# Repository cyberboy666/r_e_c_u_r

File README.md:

# r_e_c_u_r

 an open diy video sampler
 
 ![vectorfront][vectorfront]
 
__r_e_c_u_r__ is an embedded python/openframeworks application on _raspberry pi3_ that uses `input` from the _keypad_ to control  `video` while displaying a simple text ui on a _rpi lcd screen_ 

## in-depth video demo

[![video-walkthrough][video-thumbnail]](http://www.youtube.com/watch?v=FKKDr7pLpp0)

## features

- seamlessly loop video through rpi's HDMI or composite out
- intuitively _browse_ video files from external and internal disk and map them into __r_e_c_u_r__
- load and trigger video samples from numbered slots in the _sampler_ bank
- dynamically set and clear the start/end points of each sample as it plays
- control and sequence all inputs and more with midi-usb
- many sampler modes for varied playback including: repeat, one-shot, gated, random, fixed-length, random-start and more 
- exhaustive and extendable _settings_ menu  to suit your use

## extensions

as of _V2.0_ the __r_e_c_u_r__ platform has been extended in a number of directions to complement live performance and  _\_recur\__ , the original video playing engine:

- _\_captur\__ : input live video via CSI or USB , for live sampling and processing
- _\_conjur\__ : glsl shader engine, map and trigger shader files and control parameters in real time; generate video or process and mix existing sources
- _\_detour\__ : in-memory frame sampling (up to 500 frames), video scrubbing, playback speed and direction control, finger drumming
- toggling internal feedback + strobe effect 

_NOTE: most of the new V2.0 features are optimised for sd composite video output. Some of these extensions will work over HDMI but they are not fully supported - especially the live video input struggles_

### extension video walkthroughs

- [![conjur_walkthrough][conjur_thumbnail]](https://www.youtube.com/watch?v=ah2HY1fuv8w)
- [![captur_walkthrough][captur_thumbnail]](https://www.youtube.com/watch?v=e7m_YHEFahs)
- [![detour_walkthrough][detour_thumbnail]](https://www.youtube.com/watch?v=e9vrzn7c9R8)

## main objectives:

- *Affordable* : reducing the entry cost to performing with video
- *Extendable* : laying the foundations (of a user interface and code style) that can be easily iterated on by the community
- *Simple* : easy to operate (abstracted completely from ‘driving’ a raspi ) , easy to build (no technical computer install-y or circuit-y knowledge required to diy) , easy to develop (human readable code, inviting amateur/first time coders to contribute)

## documentation:

- [operating] - how to use r_e_c_u_r
- [building] - how to diy r_e_c_u_r
- [developing] - how to contribute to r_e_c_u_r

many other things documented on the [wiki]

## status

The nature of this project is to be open-ended and community driven. my r_e_c_u_r already solves the problems i initially built it for. what happens next depends on how it is used and received by you. if you like the idea please let me know / get involved !

## contact, donation and thanks

langolierz@gmail.com

you can find me (and others) at https://scanlines.xyz , an online diy av community space. theres a r_e_c_u_r channel in the chatroom: https://chat.scanlines.xyz/channel/r_e_c_u_r
there is also a facebook user group : https://www.facebook.com/groups/114465402691215/

all feedback is appreciated. if you want to donate to this project you can do so with the above email via paypal : everything i receive will go into improving __r_e_c_u_r__. cheers to Leo Browning for the 3d modelling and vector art and to Ben Caldwell for heaps of help with the code!

[vectorfront]: ./enclosure/vectorfront_keys.png
[video-thumbnail]: https://github.com/langolierz/r_e_c_u_r/wiki/images/video-thumbnail.jpg
[conjur_thumbnail]: https://github.com/langolierz/r_e_c_u_r/wiki/images/conjur_video_thumbnail.jpg
[captur_thumbnail]: https://github.com/langolierz/r_e_c_u_r/wiki/images/captur_video_thumbnail.jpg
[detour_thumbnail]: https://github.com/langolierz/r_e_c_u_r/wiki/images/detour_video_thumbnail.jpg
[operating]: https://github.com/langolierz/r_e_c_u_r/wiki/operate_docs
[building]: https://github.com/langolierz/r_e_c_u_r/wiki/build_docs
[developing]: https://github.com/langolierz/r_e_c_u_r/wiki/develop_docs
[wiki]: https://github.com/langolierz/r_e_c_u_r/wiki

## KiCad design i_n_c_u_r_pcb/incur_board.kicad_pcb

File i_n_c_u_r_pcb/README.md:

# i_n_c_u_r extension files have moved

you can now find all info and source regarding the i_n_c_u_r circuit [here](https://github.com/cyberboy666/i_n_c_u_r)

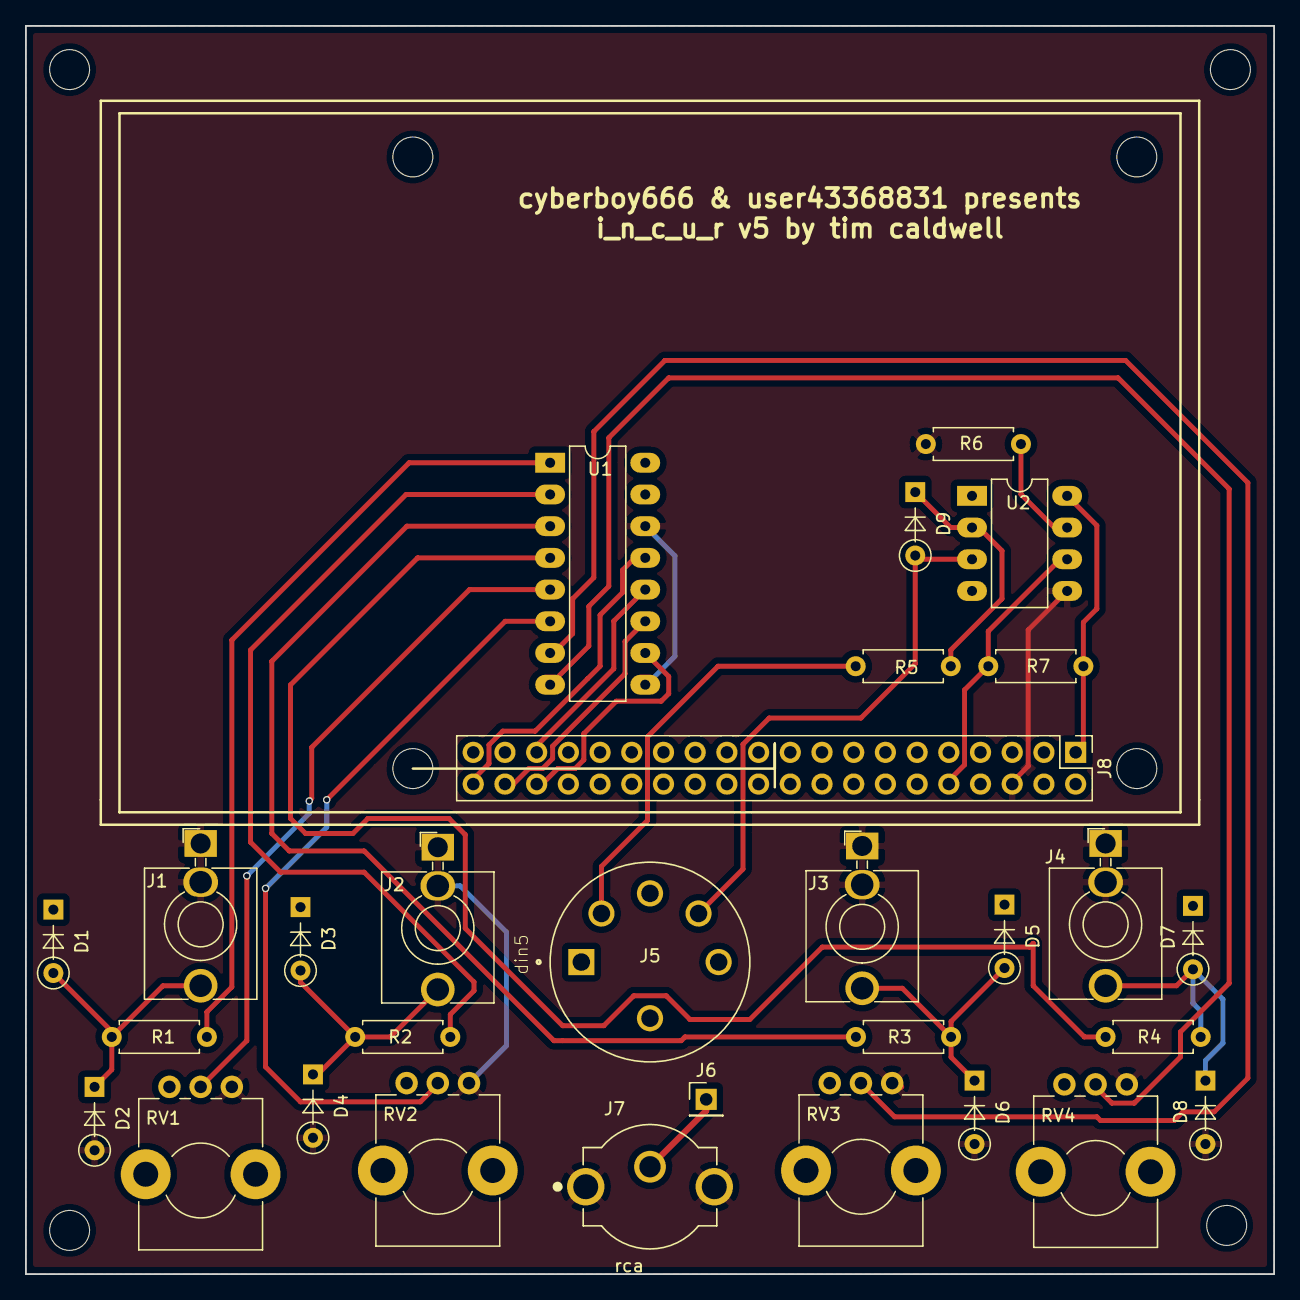
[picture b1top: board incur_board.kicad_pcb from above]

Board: 2 copper layers, 100.0 x 100.0 mm, 30 parts (0 on the bottom side), 25 nets.

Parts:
D1, D2, D3, D4, D5, D6, D7, D8: BAT46; D_DO-35_SOD27_P5.08mm_Vertical_KathodeUp
D9: 1N4148; D_DO-35_SOD27_P5.08mm_Vertical_KathodeUp
J1, J2, J3, J4: mono_jack_3.5mm; Jack_3.5mm_QingPu_WQP-PJ398SM_Vertical_CircularHoles
J5: din5; tht_vertical_din5
J6: Conn_01x01; Pin_Header_Straight_1x01_Pitch2.54mm
J7: rca; tht_rca_vertical
J8: 2x20_Extra_Tall_Header; PinHeader_2x20_P2.54mm_Vertical
R1, R2, R3, R4: 1K; R_Axial_DIN0207_L6.3mm_D2.5mm_P7.62mm_Horizontal
R5: 220; R_Axial_DIN0207_L6.3mm_D2.5mm_P7.62mm_Horizontal
R6: 100K; R_Axial_DIN0207_L6.3mm_D2.5mm_P7.62mm_Horizontal
R7: 470; R_Axial_DIN0207_L6.3mm_D2.5mm_P7.62mm_Horizontal
RV1, RV2, RV3, RV4: 10k_pot; tht_vertical_potentiometer
U1: MCP3008; DIP-16_W7.62mm_LongPads
U2: 6N138; DIP-8_W7.62mm_LongPads

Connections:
+3V3: J8.1, R7.2, U2.8
+5V: D1.1, D3.1, D5.1, D7.1, J8.2, RV1.1, RV2.1, RV3.1, RV4.1, U1.15, U1.16
A_IN_0: R1.1, U1.1
A_IN_1: R2.1, U1.2
A_IN_2: R3.1, U1.3
A_IN_3: R4.1, U1.4
A_IN_4: RV1.2, U1.5
A_IN_5: RV2.2, U1.6
A_IN_6: RV3.2, U1.7
A_IN_7: RV4.2, U1.8
CLK: J8.40, U1.13
CS: J8.36, U1.10
D_IN: J8.38, U1.11
D_OUT: J8.35, U1.12
GND: D2.2, D4.2, D6.2, D8.2, J1.2, J1.3, J2.2, J2.3, J3.2, J3.3, J4.2, J4.3, J7.2, J8.6, R6.1, RV1.3, RV2.3, RV3.3, RV4.3, U1.9, U1.14, U2.5
unnamed: D1.2, D2.1, J1.1, R1.2
unnamed: D3.2, D4.1, J2.1, R2.2
unnamed: D5.2, D6.1, J3.1, R3.2
unnamed: D7.2, D8.1, J4.1, R4.2
unnamed: D9.1, R5.1, U2.2
unnamed: D9.2, J5.5, U2.3
unnamed: J5.4, R5.2
unnamed: J6.1, J7.1
unnamed: R6.2, U2.7
RX: J8.10, R7.1, U2.6

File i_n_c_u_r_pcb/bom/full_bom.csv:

sku,qty,ref,val
A-1095,8,D1 D2 D3 D4 D5 D6 D7 D8 ,BAT46
A-157,1,D9 ,1N4148
A-2563,4,J1 J2 J3 J4 ,mono_jack_3.5mm
490-SD-50BV,1,J5 ,din5
-,1,J6 ,Conn_01x01
490-RCJ-024,1,J7 ,rca
485-1979,1,J8 ,2x20_Extra_Tall_Header
A-2200,4,R1 R2 R3 R4 ,1K
A-2246,1,R5 ,220
A-2248,1,R6 ,100K
A-2247,1,R7 ,470
652-PTV09A-4025FB103,4,RV1 RV2 RV3 RV4 ,10k_pot
A-2470,1,U1 ,MCP3008
859-6N138,1,U2 ,6N138

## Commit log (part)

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2019-09-08 Create notes_on_demo_video
2019-09-08 Rename notes_on_demo_video to notes_on_demo_video.md
2019-11-29 wip new shader banks feature
2019-12-03 adding strobe feature
2019-12-06 fixing update code
2019-12-07 map generic bank/slot midi command eg 'play_shader_0_0' to method
2019-12-08 v minor update
2019-12-09 experimental branch for implementing "akai apc key 25" visual feedback by lighting the led buttons to indicate shaders playing (early test)
2019-12-09 update svgs
2019-12-10 fix shader layer offset problem
2019-12-11 fix update code
2019-12-12 still untested, but think this should turn off all LEDs corresponding to unselected slots, while turning on the LEDs for selected slots
2019-12-13 its rough, but it works to indicate the currently playing shader on each layer!
2019-12-13 indicate which shader layer is selected by flashing the 'send' button. you can move up/down layers using 'send'/'device' respectively.
2019-12-14 merged and sorts shaders now too
2019-12-14 added toggle_x3_as_speed as a command available to midi map, and added a script to generate a helpful list of available actions
2019-12-14 Adds ability to have alternative MIDI mappings trigger when FN is held down. Use eg FN_DEFAULT to specify
2019-12-14 Feedback when camera preview is on
2019-12-15 fix boot bug
2019-12-15 Rough 'plugin' architecture, only supporting MIDI feedback right now
2019-12-15 Fix wrong indicator of 'preview' mode
2019-12-15 example of a macro running in a midi actions plugin
2019-12-15 'run_automation' example that triggers parameter changes
2019-12-15 MidiActionsPlugin -> ActionsPlugin, SequencePlugin has toggle functions (pause doesn't quite work right so need to come back and fix this)
2019-12-16 slight tidy and add pause_automation command separate from toggle_pause_automation (which still doesnt work like intended)
2019-12-17 Added base methods for plugin types that throw NotImplementedError if not overridden
2019-12-18 halfway to having working 'shader preset' banks
2019-12-19 fix argument order in plugins too
2019-12-19 ahhh fixed the bug!!! midi-mapped presets basically work now!
2019-12-19 Presets are now persisted between boots! With save/load json folder for plugins. Also fixed shader feedback state not updatingx
2019-12-19 SequencePlugin loops now
2019-12-19 move the routes back because they dont work, friendlier error message when no method found to handle route
2019-12-20 whew! record and playback shader automation parameters and persist to disk
2019-12-20 dont switch shaders if already selected
2019-12-21 stage 1 refactor shader param frame handling
2019-12-21 next stage refactor
2019-12-22 fix last (ha!) bug with recording loop automation, tidy up debug output
2019-12-22 wip osc and node server
2019-12-22 basic apc feedback for automation clips
2019-12-22 refactor some things
2019-12-22 fix range of param routes, add better debugging if no action found
2019-12-23 none-working
2019-12-23 osc responds to values 0-1 now
2019-12-23 tidy up
2019-12-23 renamed
2019-12-23 remove some crap from sight
2019-12-23 better control & feedback for shader quick presets (clear_current_frame and feedback indicates empty/selected slots)
2019-12-23 improve feedback
2019-12-24 improved generate-list-actions output
2019-12-24 improved generate-list-actions and added pregenerated documentation
2019-12-24 Improved auto-generated actions
2019-12-24 strip out some less-useful actions
2019-12-24 remove try_remove_file
2019-12-24 store/recall x3_as_speed setting in macros/automation
2019-12-24 fix some bugs that had crept in during refactoring
2019-12-24 presets/automation stores strobe amount too now
2019-12-25 ffix action names, tidy up a little, added midi mappings for modulation to shift+knob4-7, untested
2019-12-27 updated ACTIONS.md
2019-12-27 backported enable_feedback and disable_feedback commands
2019-12-27 fix modulation
2019-12-27 mappings for external osc sound reactivity
2019-12-27 tidy up some debug output, do quick checks first in get_ignored
2019-12-27 4 modulation inputs, effect levels assignable per-slot-per-layer, averages together modulation values from multiple sources
2019-12-27 remove debug output
2019-12-28 update docs to reflect new modulation changes
2019-12-28 quick little python script to read from microphone/line in and output OSC volume
2019-12-28 reset_modulation and reset_selected_modulation methods to help stay sane
2019-12-30 working proof of concept sending commands to an Arduino via serial (for use with https://github.com/doctea/veboard)
2020-01-01 send random commands to the serial device
2020-01-03 can send strings directly from midi mappings etc as routes accept strings now
2020-01-03 run soundreact along with recur
2020-01-05 adding to osc support
2020-01-05 remove FN_DEFAULT functionality since it is redundant, fixed config file
2020-01-05 more removal of redundant 'FN_DEFAULT' functionality
2020-01-05 re-add generic osc route
2020-01-10 log conjur output to a separate file
2020-01-10 Backported basic code for MIDI controller autodetection (custom config file per controller), plugins with example plugin, and Akai APC Key 25 feedback plugin
2020-01-10 enable the example test plugin
2020-01-10 tidied up a little
2020-01-10 fs tables
2020-01-14 can adjust speed of sequences by binding set_automation_speed, range is -2.0x to +2.0x
2020-01-14 update actions doc
2020-01-14 missed necessary file for midi input detection! also fix midi feedback not working if the shader plugins are not installed
2020-01-19 fix to prevent crash when non-APC Key was connected! silly typo
2020-01-19 Rough Launchpad custom controls with feedback
2020-01-31 rename MidiActionsTestPlugin to generic TestPlugin, remove mention of it in feedback plugin
2020-01-31 MultiActionsPlugin to allow mapping multiple actions to one binding using && to separate actions, eg action_1&&action_2
2020-01-31 updated ACTIONS docs
2020-01-31 Another simple plugin adding ability to append "|invert" to a mapping to invert the value.
2020-01-31 can save value to variable using `set_variable_VARIABLENAME1` and then recall that variable in a mapping using eg set_the_shader_param_0_layer_offset_0_continuous<VARIABLENAME1
2020-02-01 small fix for midi status command crash when no midi device connected
2020-02-02 new! visual representation of the modulation parameter levels on the shader bank screen so you can see what levels are mapped to which parameters and which modulation slot is selected ("a b C d" for 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
2020-02-08 fix for shader layer selection not getting note mappingx in MidiFeedback plugins
2020-02-08 queued output, ensures most recent value change is always sent
2020-02-08 WJ Send can control mix now, more flexibility in sending commands via mappings
2020-02-08 Backported WJSendPlugin for controlling Panasonic video mixers - tested on WJ-MX30, but probably works for the MX50 and AVEs, too
2020-02-08 plugins can now add pages to the recur display, using DisplayPlugin as base
2020-02-09 controls for MANIPULA page
2020-02-09 minor tidyup + fix syntax error in config
2020-02-11 ModulationReceiverPlugin that allows plugin to receive when the modulation slots A-D (1-4) value changes... with quick hack to WJSendPlugin to wiggle some parameters in response
2020-02-12 Fix osc input so it listens to the network again, commented-out stub for showing clip progress in leds (doesnt work too well so not enabled)
2020-02-15 stubs for possible better mapping of WJ MX controls
2020-02-16 AutomationSourcePlugin type, to enable recording of WJ params to automation clips (featured in feature_plugin_shader_gadgets)
2020-02-16 loop recording now saves plugin AutomationSources (eg WJSendPlugin!)
2020-02-16 tidy up display control mappings and other fixes
2020-02-16 fix for QuickPresetPlugin not saving into correct slot
2020-02-16 fixes on WJSendPlugin side for automation recording (overdubs)
2020-02-16 move more frame stuff into plugin
2020-02-16 minor update to display
2020-02-20 Experimental (but appears to be working) smoothing of automation clip shader params. todo: save smoothed version, smooth plugins, smooth WJSend..
2020-02-20 WJSendPlugin stores args, so will be able to interpolate between values...
2020-02-21 fix extraneous commands sent
2020-02-21 fix binding of LFO plugin on/off
2020-02-21 tidy up LFOModulation to make it easier to add selectable formulas later
2020-02-21 improvements to LFOModulation plugin - speed control, tidy up
2020-02-22 Overhaul of WJSendPlugin to define parameters programmatically and so enable modulation
2020-02-22 couple bugfixes
2020-02-23 make wj send modulation sane again
2020-02-23 drop extra 00 on VCC since it hasnt helped anyway
2020-02-24 add settings for osc, accesspoint and remote server
2020-02-24 eject usb setting
2020-02-29 SoundReactPlugin that has assignable modulation from different processing of input signal, without using external helper script.
2020-02-29 Make numpad input use actions the same as midi input etc, so that plugins can extend numpad functionality
2020-02-29 Save settings json on program quit -- shader modulation levels moved into settings data so they persist across restarts
2020-02-29 plugins are notified of exiting so they can save config etc
2020-02-29 Fix for output plugins now MIDI port detection is fixed (variable name changed)
2020-02-29 wj_reset_modulation action to reset all modulation levels set in WJSendPlugin.
2020-02-29 "set_display_mode_settings" etc to switch display screen, thanks to https://github.com/sebiik for the idea
2020-03-01 wip: trigger changes when peak level changse significantly from the average
2020-03-01 Don't barf on MOUSE_INPUT if it doesn't exist in config
2020-03-01 adding plugin menu
2020-03-01 plugin selection persists
2020-03-01 tidy up + change way plugins are found+listed, solves some problems, plugins use the active status to indicate disabled and now have start/stop methods (seems to work to stop+restart Sound+WJ ok, nee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
2020-03-07 tidy up some old code and add some comments
2020-03-07 Tidyups to make showing bar graphics easier, ShaderQuickPresetPlugin has a display page that summarises the currently selected preset, Frame knows how to summarise stuff for display
2020-03-07 allow display modes to fallback to other display modes before default
2020-03-08 renamed 'active' to 'enabled' when it comes to plugins
2020-03-08 can activate/deactivate WJSendPlugin without disabling
2020-03-08 overhaul mod bank screen (not sure its better tho), lfomodulation and modulation values saved with presets, refactor some frame stuff to make more readable & maintainable
2020-03-10 helper functions for getting variables from ManipulatePlugin into other parts of recur code
2020-03-12 fixed osc bugs, midi lag bugs, midi cc buttons
2020-03-12 Show error when trying to fast-switch page that isn't there
2020-03-12 plugins summarise their frame data for display (LFOModulation, rudimentary WJMXSend altho cant see it working?), LFOModulation should save+recall active state and speed now too?
2020-03-13 profiler script
2020-03-14 trying to fix from the merge..
2020-03-14 updated mappings and small fixes
2020-03-14 couple more tweaks, still a problem if you prses '9' too soon before '4' when quick switching, annoying but live with it for now
2020-03-15 multithread WJSend to stop it impacting upon the rest of recur UI performance
2020-03-15 switch shader layers using <> on shader mod page, since ui looks like it says thats possible
2020-03-16 update ACTIONS
2020-03-16 improve mod bank page UI slightly
2020-03-16 default keypad mappings to use the recently added actions and make some screens more usable without setting up midi mappings
2020-03-16 updated ACTIONS and DEFAULT_CONTROLS.txt
2020-03-18 better saving of plugins / midifeedback should turn lights off when its done
2020-03-18 fix DEFAULT_CONTROLS problems + update
2020-04-12 Fix for WJSendPlugin not quitting if it wasn't loaded properly?
2020-04-18 updated ACTIONS and DEFAULT_CONTROLS docs
2020-05-01 Fix assignment
2020-05-01 Whitespace
2020-05-02 tracked experimental veboard serial send plugin
2020-05-24 Dont show hidden files in browser
2020-05-24 ok, fix files for videos not just shaders!
2020-07-23 expose video-positioning action seek_to_location_on_player - hopefully helps with #142 ?
2020-07-23 improve manipulate plugin a little, has rand() and better access to sin cos etc, examples in json_objects/midi_action_mapping_APC Key 25.json
2021-03-15 fix WJSendPlugin so that it doesn't crash if it can't open a serial device
